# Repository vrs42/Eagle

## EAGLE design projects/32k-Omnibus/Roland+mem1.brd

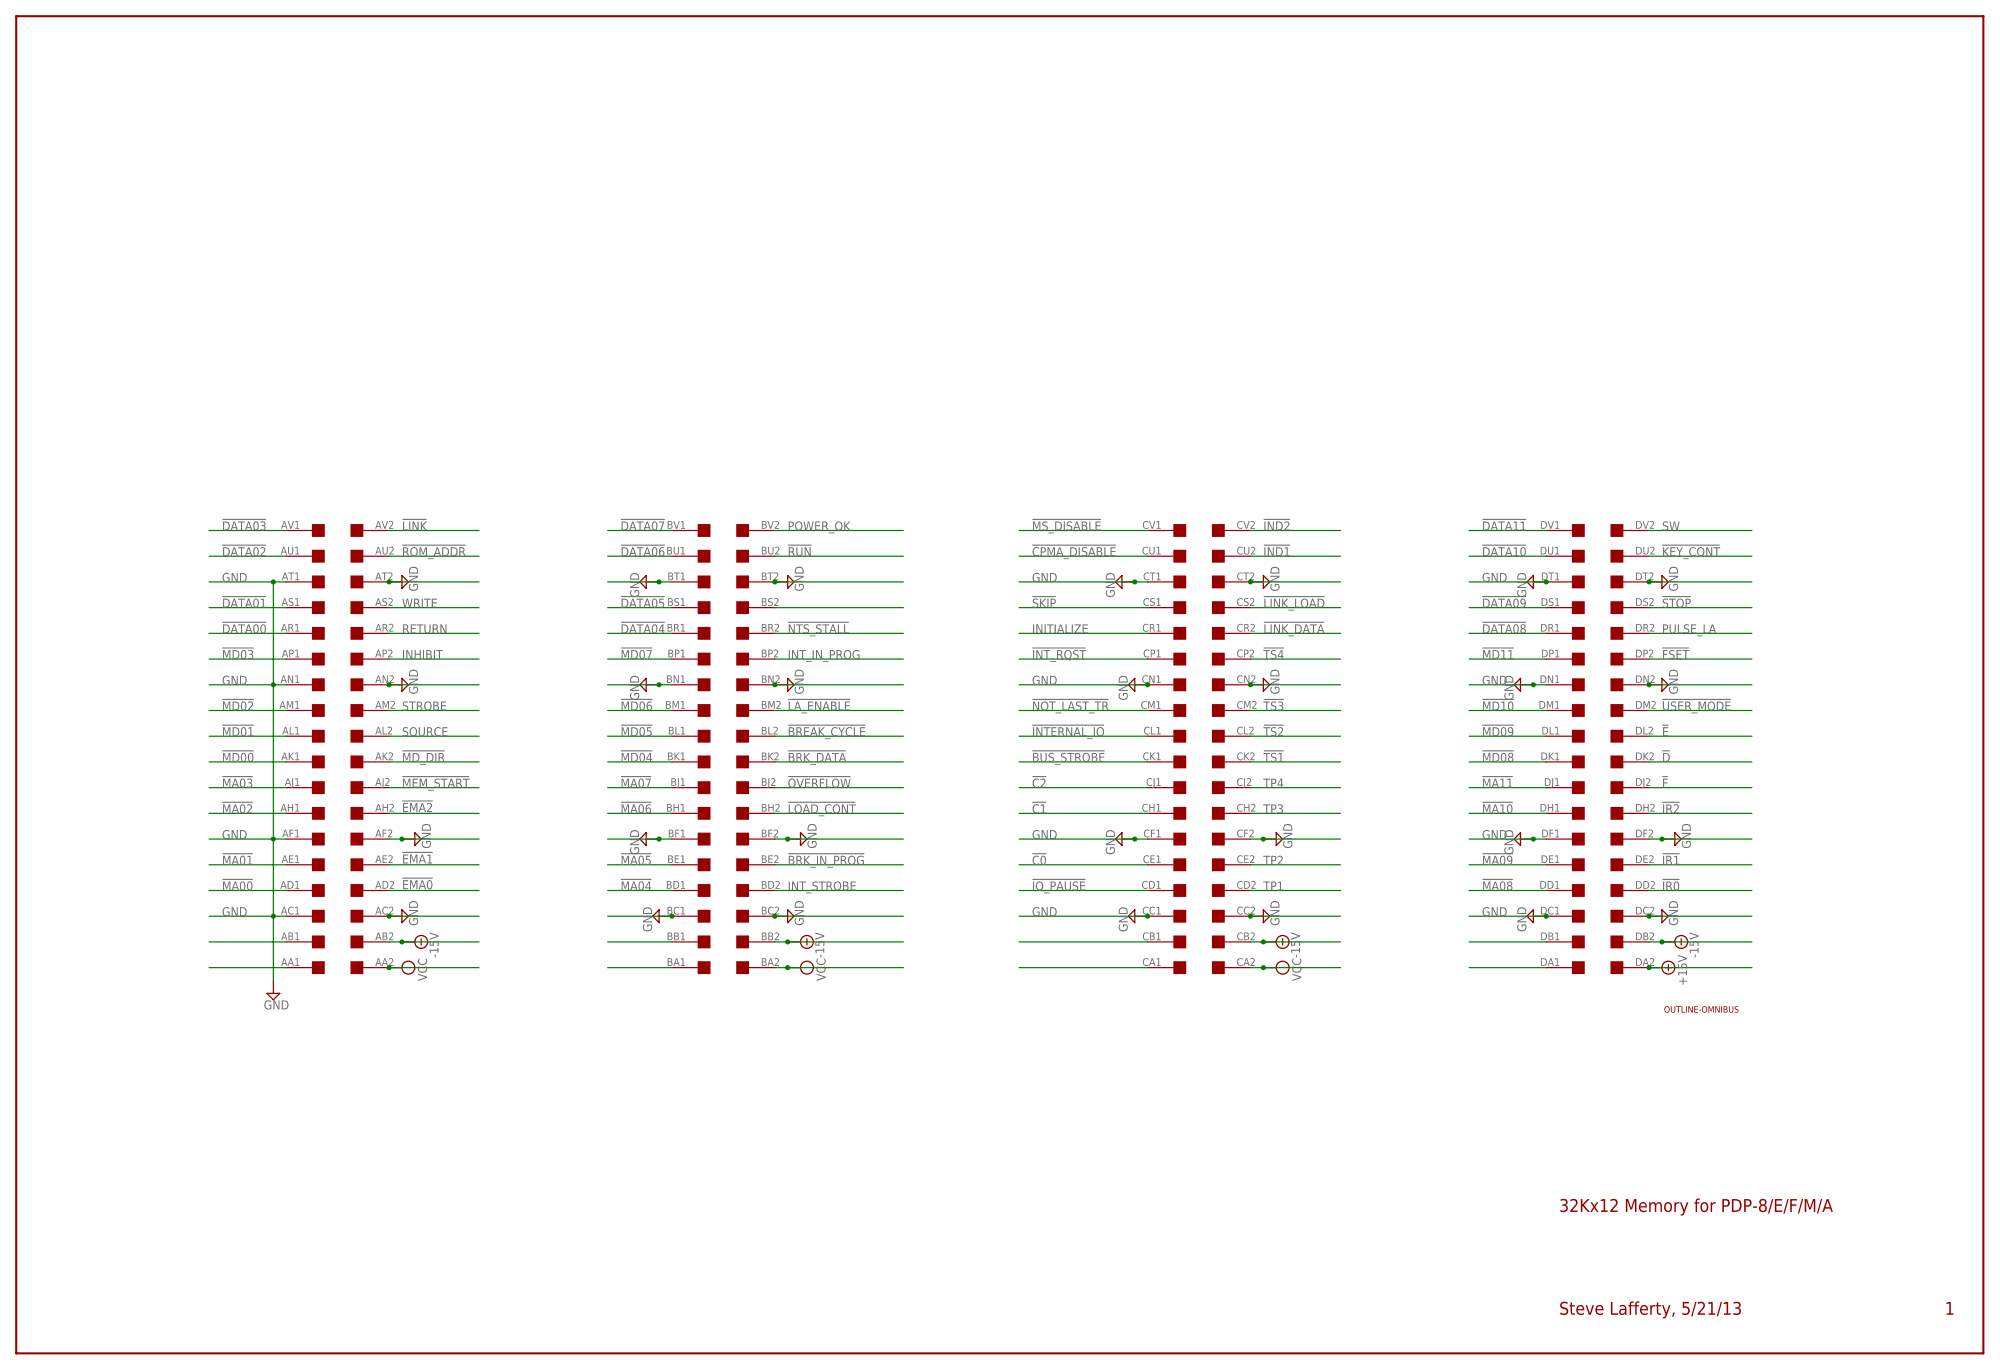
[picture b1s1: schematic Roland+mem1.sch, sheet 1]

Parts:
J1: EDGE; EDGE-CON8
U$1: OUTLINE-OMNIBUS; OMNIBUS

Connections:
!BREAK_CYCLE: J1.BL2
!BRK_DATA: J1.BK2; also elsewhere on the board
!BRK_IN_PROG: J1.BE2
!BUS_STROBE: J1.CK1
!C0: J1.CE1
!C1: J1.CH1
!C2: J1.CJ1
!CPMA_DISABLE: J1.CU1
!D: J1.DK2
!DATA00: J1.AR1; also elsewhere on the board
!DATA01: J1.AS1; also elsewhere on the board
!DATA02: J1.AU1; also elsewhere on the board
!DATA03: J1.AV1; also elsewhere on the board
!DATA04: J1.BR1; also elsewhere on the board
!DATA05: J1.BS1; also elsewhere on the board
!DATA06: J1.BU1; also elsewhere on the board
!DATA07: J1.BV1; also elsewhere on the board
!DATA08: J1.DR1; also elsewhere on the board
!DATA09: J1.DS1; also elsewhere on the board
!DATA10: J1.DU1; also elsewhere on the board
!DATA11: J1.DV1; also elsewhere on the board
!E: J1.DL2
!EMA0: J1.AD2; also elsewhere on the board
!EMA1: J1.AE2; also elsewhere on the board
!EMA2: J1.AH2; also elsewhere on the board
!F: J1.DJ2
!FSET: J1.DP2
!IND1: J1.CU2
!IND2: J1.CV2
!INTERNAL_IO: J1.CL1
!INT_RQST: J1.CP1
!IO_PAUSE: J1.CD1
!IR0: J1.DD2
!IR1: J1.DE2
!IR2: J1.DH2
!KEY_CONT: J1.DU2; also elsewhere on the board
!LA_ENABLE: J1.BM2; also elsewhere on the board
!LINK: J1.AV2
!LINK_DATA: J1.CR2
!LINK_LOAD: J1.CS2
!LOAD_CONT: J1.BH2
!MA00: J1.AD1; also elsewhere on the board
!MA01: J1.AE1; also elsewhere on the board
!MA02: J1.AH1; also elsewhere on the board
!MA03: J1.AJ1; also elsewhere on the board
!MA04: J1.BD1; also elsewhere on the board
!MA05: J1.BE1; also elsewhere on the board
!MA06: J1.BH1; also elsewhere on the board
!MA07: J1.BJ1; also elsewhere on the board
!MA08: J1.DD1; also elsewhere on the board
!MA09: J1.DE1; also elsewhere on the board
!MA10: J1.DH1; also elsewhere on the board
!MA11: J1.DJ1; also elsewhere on the board
!MD00: J1.AK1; also elsewhere on the board
!MD01: J1.AL1; also elsewhere on the board
!MD02: J1.AM1; also elsewhere on the board
!MD03: J1.AP1; also elsewhere on the board
!MD04: J1.BK1; also elsewhere on the board
!MD05: J1.BL1; also elsewhere on the board
!MD06: J1.BM1; also elsewhere on the board
!MD07: J1.BP1; also elsewhere on the board
!MD08: J1.DK1; also elsewhere on the board
!MD09: J1.DL1; also elsewhere on the board
!MD10: J1.DM1; also elsewhere on the board
!MD11: J1.DP1; also elsewhere on the board
!MD_DIR: J1.AK2; also elsewhere on the board
!MEM_START: J1.AJ2; also elsewhere on the board
!MS_DISABLE: J1.CV1; also elsewhere on the board
!NOT_LAST_TR: J1.CM1
!NTS_STALL: J1.BR2
!OVERFLOW: J1.BJ2
!ROM_ADDR: J1.AU2; also elsewhere on the board
!RUN: J1.BU2; also elsewhere on the board
!SKIP: J1.CS1
!STOP: J1.DS2; also elsewhere on the board
!TS1: J1.CK2
!TS2: J1.CL2
!TS3: J1.CM2
!TS4: J1.CP2; also elsewhere on the board
!USER_MODE: J1.DM2
+15V: J1.DA2
-15V: J1.AB2, J1.BB2, J1.CB2, J1.DB2
GND: J1.AC1, J1.AC2, J1.AF1, J1.AF2, J1.AN1, J1.AN2, J1.AT1, J1.AT2, J1.BC1, J1.BC2, J1.BF1, J1.BF2, J1.BN1, J1.BN2, J1.BT1, J1.BT2, J1.CC1, J1.CC2, J1.CF1, J1.CF2, J1.CN1, J1.CN2, J1.CT1, J1.CT2, J1.DC1, J1.DC2, J1.DF1, J1.DF2, J1.DN1, J1.DN2, J1.DT1, J1.DT2; also elsewhere on the board
INHIBIT: J1.AP2
INITIALIZE: J1.CR1; also elsewhere on the board
INT_IN_PROG: J1.BP2
INT_STROBE: J1.BD2
POWER_OK: J1.BV2; also elsewhere on the board
PULSE_LA: J1.DR2; also elsewhere on the board
RETURN: J1.AR2
SOURCE: J1.AL2; also elsewhere on the board
STROBE: J1.AM2
SW: J1.DV2; also elsewhere on the board
TP1: J1.CD2
TP2: J1.CE2
TP3: J1.CH2
TP4: J1.CJ2; also elsewhere on the board
VCC: J1.AA2, J1.BA2, J1.CA2; also elsewhere on the board
WRITE: J1.AS2; also elsewhere on the board

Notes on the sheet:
32Kx12 Memory for PDP-8/E/F/M/A
Steve Lafferty, 5/21/13

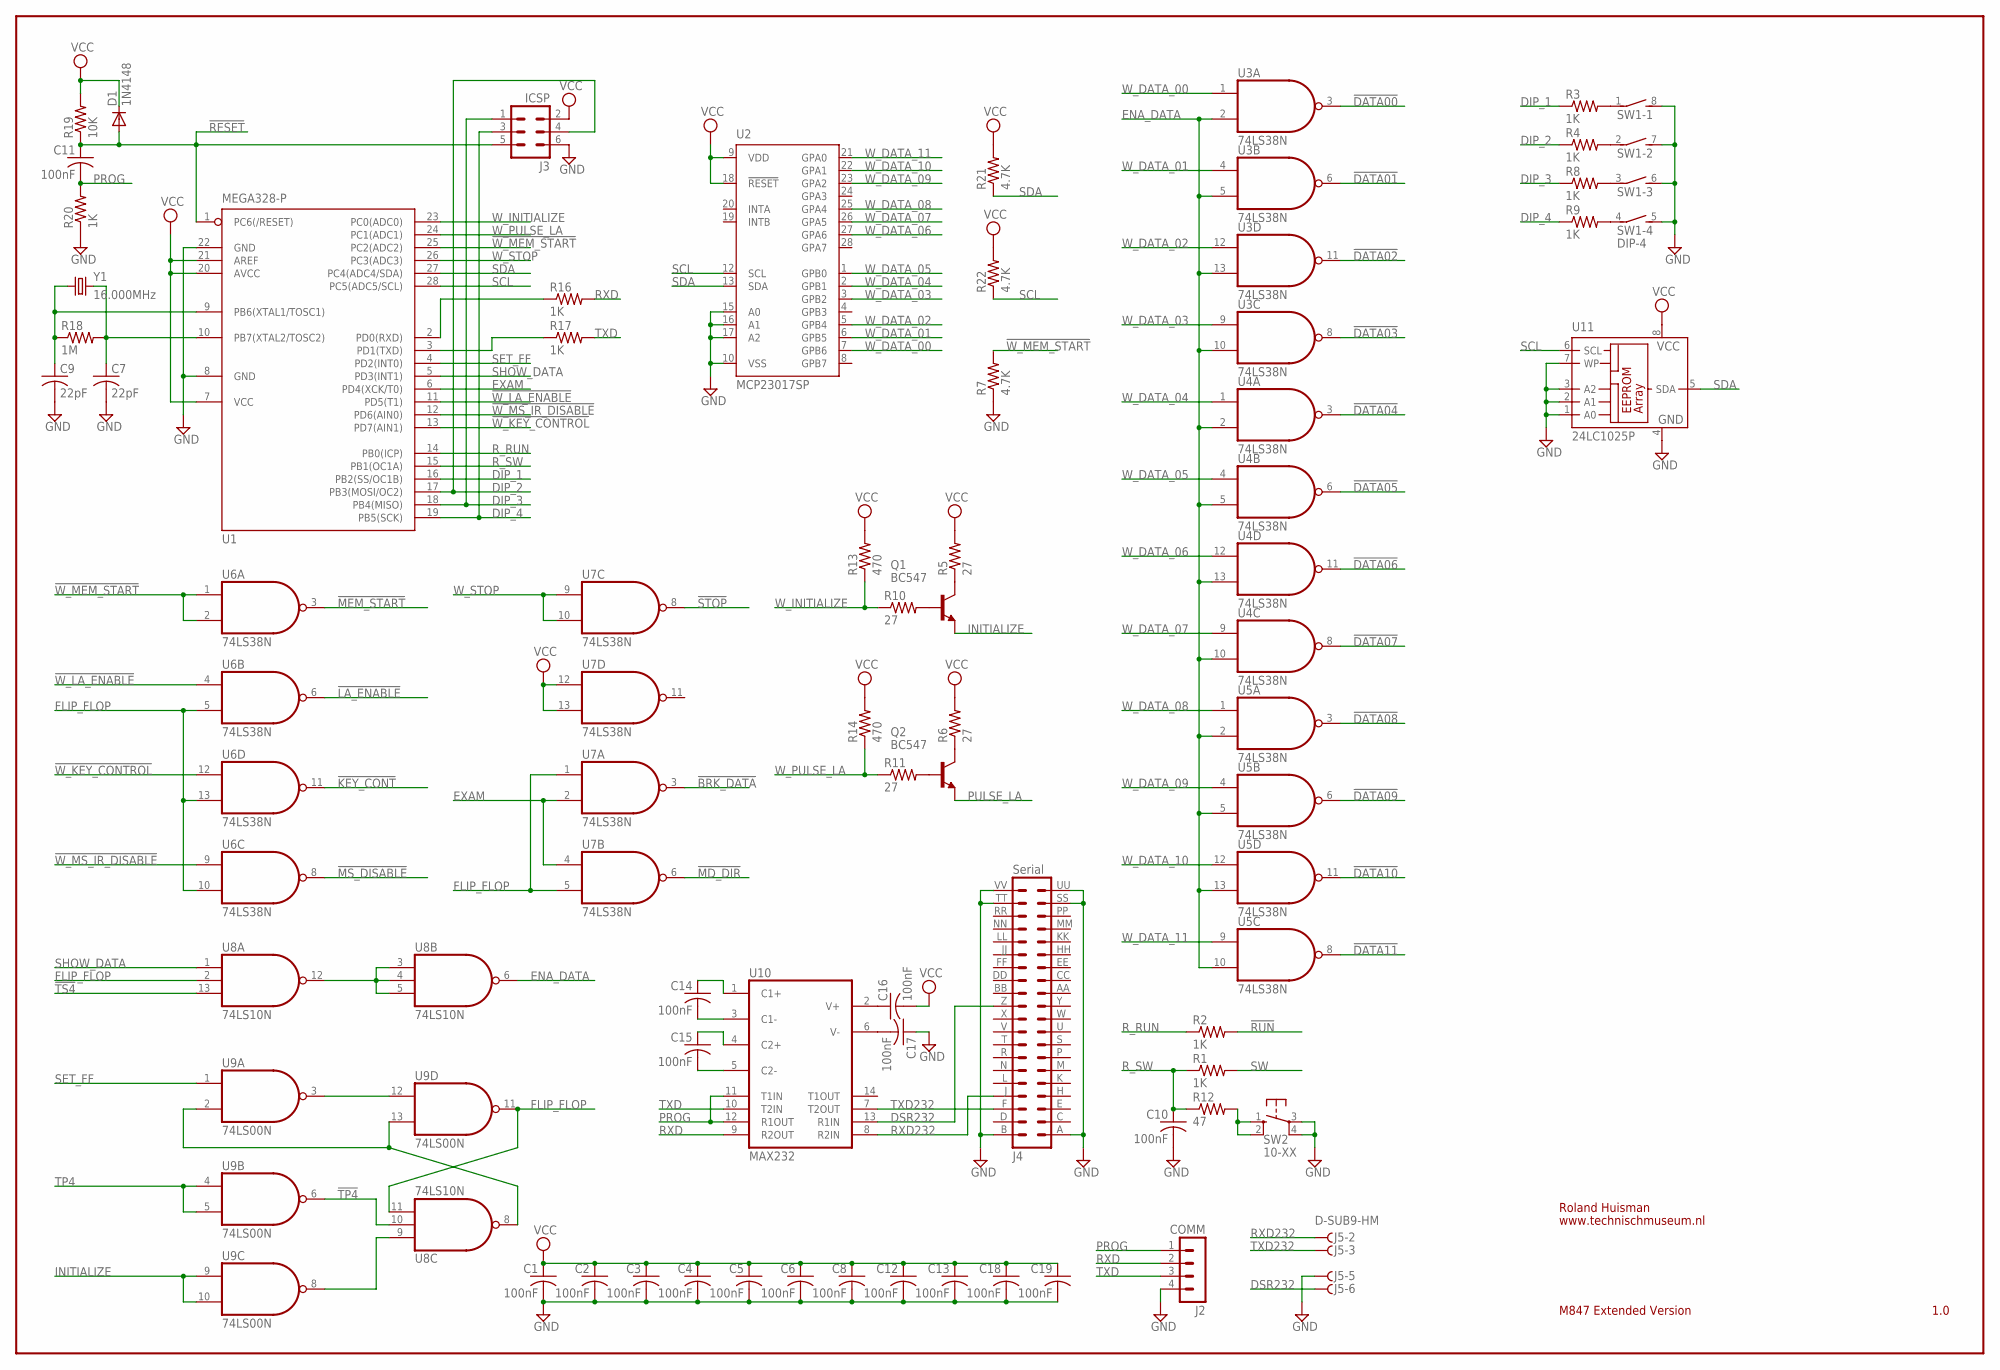
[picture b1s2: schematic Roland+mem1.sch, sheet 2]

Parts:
C1, C2, C3, C4, C5, C6, C8, C10, C11, C12, C13, C14, C15, C16, C17, C18, C19: 100nF; C050-025X075
C7, C9: 22pF; C050-025X075
D1: 1N4148; DO35-10
J2: COMM; MA04-1
J3: ICSP; MA03-2
J4: Serial; DEC40PINH
J5: D-SUB9-HM; H5M09RA
Q1, Q2: BC547; TO5
R1, R2, R3, R4, R8, R9, R16, R17, R20: 1K; 0207/10
R5, R6, R10, R11: 27; 0207/10
R7, R21, R22: 4.7K; 0207/10
R12: 47; 0207/10
R13, R14: 470; 0207/10
R18: 1M; 0207/10
R19: 10K; 0207/10
SW1: DIP-4; DIP04S
SW2: 10-XX; B3F-10XX
U1: MEGA328-P; DIL28-3
U2: MCP23017SP; DIL28-3
U3, U4, U5, U6, U7: 74LS38N; DIL14
U8: 74LS10N; DIL14
U9: 74LS00N; DIL14
U10: MAX232; DIL16
U11: 24LC1025P; DIL8
Y1: 16.000MHz; HC49U-H

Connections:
!BRK_DATA: U7.3 (O); also elsewhere on the board
!DATA00: U3.3 (O); also elsewhere on the board
!DATA01: U3.6 (O); also elsewhere on the board
!DATA02: U3.11 (O); also elsewhere on the board
!DATA03: U3.8 (O); also elsewhere on the board
!DATA04: U4.3 (O); also elsewhere on the board
!DATA05: U4.6 (O); also elsewhere on the board
!DATA06: U4.11 (O); also elsewhere on the board
!DATA07: U4.8 (O); also elsewhere on the board
!DATA08: U5.3 (O); also elsewhere on the board
!DATA09: U5.6 (O); also elsewhere on the board
!DATA10: U5.11 (O); also elsewhere on the board
!DATA11: U5.8 (O); also elsewhere on the board
!KEY_CONT: U6.11 (O); also elsewhere on the board
!LA_ENABLE: U6.6 (O); also elsewhere on the board
!MD_DIR: U7.6 (O); also elsewhere on the board
!MEM_START: U6.3 (O); also elsewhere on the board
!MS_DISABLE: U6.8 (O); also elsewhere on the board
!RESET: C11.1, D1.A, J3.5, R19.1, U1.1 (PC6(/RESET))
!RUN: R2.2; also elsewhere on the board
!STOP: U7.8 (O); also elsewhere on the board
!TP4: U8.10 (I1), U9.6 (O)
!TS4: U8.13 (I2); also elsewhere on the board
!W_KEY_CONTROL: U1.13 (PD7(AIN1)), U6.12 (I0)
!W_LA_ENABLE: U1.11 (PD5(T1)), U6.4 (I0)
!W_MEM_START: R7.2, U1.25 (PC2(ADC2)), U6.1 (I0), U6.2 (I1)
!W_MS_IR_DISABLE: U1.12 (PD6(AIN0)), U6.9 (I0)
DIP_1: R3.1, U1.16 (PB2(SS/OC1B))
DIP_2: J3.4, R4.1, U1.17 (PB3(MOSI/OC2))
DIP_3: J3.1, R8.1, U1.18 (PB4(MISO))
DIP_4: J3.3, R9.1, U1.19 (PB5(SCK))
DSR232: J4.Z (22), J5.6, U10.13 (R1IN)
ENA_DATA: U3.2 (I1), U3.5 (I1), U3.10 (I1), U3.13 (I1), U4.2 (I1), U4.5 (I1), U4.10 (I1), U4.13 (I1), U5.2 (I1), U5.5 (I1), U5.10 (I1), U5.13 (I1), U8.6 (O)
EXAM: U1.6 (PD4(XCK/T0)), U7.2 (I1), U7.4 (I0)
FLIP_FLOP: U6.5 (I1), U6.10 (I1), U6.13 (I1), U7.1 (I0), U7.5 (I1), U8.2 (I1), U8.11 (I2), U9.11 (O)
GND: C1.2, C2.2, C3.2, C4.2, C5.2, C6.2, C7.2, C8.2, C9.2, C10.2, C12.2, C13.2, C17.1, C18.2, C19.2, J2.4, J3.6, J4.A (1), J4.B (2), J4.SS (37), J4.TT (38), J4.UU (39), J4.VV (40), J5.5, R7.1, R20.1, SW1.5 (2), SW1.6 (2), SW1.7 (2), SW1.8 (2), SW2.3, SW2.4 (P1), U1.8 (GND), U1.22 (GND), U2.10 (VSS), U2.15 (A0), U2.16 (A1), U2.17 (A2), U3.7 (GND), U4.7 (GND), U5.7 (GND), U6.7 (GND), U7.7 (GND), U8.7 (GND), U9.7 (GND), U10.15 (GND), U11.1 (A0), U11.2 (A1), U11.3 (A2), U11.4 (GND), U11.7 (WP); also elsewhere on the board
INITIALIZE: Q1.1 (E), U9.9 (I0), U9.10 (I1); also elsewhere on the board
unnamed: C7.1, R18.2, U1.10 (PB7(XTAL2/TOSC2)), Y1.1
unnamed: C9.1, R18.1, U1.9 (PB6(XTAL1/TOSC1)), Y1.2
unnamed: Q1.3 (C), R5.1
unnamed: Q1.2 (B), R10.2
unnamed: Q2.3 (C), R6.1
unnamed: Q2.2 (B), R11.2
unnamed: U9.3 (O), U9.12 (I0)
unnamed: U8.3 (I0), U8.4 (I1), U8.5 (I2), U8.12 (O)
unnamed: U8.8 (O), U9.2 (I1), U9.13 (I1)
unnamed: R17.1, U1.3 (PD1(TXD))
unnamed: R16.1, U1.2 (PD0(RXD))
unnamed: U8.9 (I0), U9.8 (O)
unnamed: C17.2, U10.6 (V-)
unnamed: C14.1, U10.1 (C1+)
unnamed: C14.2, U10.3 (C1-)
unnamed: C15.2, U10.5 (C2-)
unnamed: C15.1, U10.4 (C2+)
unnamed: C16.1, U10.2 (V+)
unnamed: R12.2, SW2.1 (S), SW2.2 (S1)
unnamed: R3.2, SW1.1
unnamed: R4.2, SW1.2 (1)
unnamed: R8.2, SW1.3 (1)
unnamed: R9.2, SW1.4 (1)
PROG: C11.2, J2.1, R20.2, U10.11 (T1IN), U10.12 (R1OUT)
PULSE_LA: Q2.1 (E); also elsewhere on the board
RXD: J2.2, R16.2, U10.9 (R2OUT)
RXD232: J4.J (8), J5.2, U10.8 (R2IN)
R_RUN: R2.1, U1.14 (PB0(ICP))
R_SW: C10.1, R1.1, R12.1, U1.15 (PB1(OC1A))
SCL: R22.1, U1.28 (PC5(ADC5/SCL)), U2.12 (SCL), U11.6 (SCL)
SDA: R21.1, U1.27 (PC4(ADC4/SDA)), U2.13 (SDA), U11.5 (SDA)
SET_FF: U1.4 (PD2(INT0)), U9.1 (I0)
SHOW_DATA: U1.5 (PD3(INT1)), U8.1 (I0)
SW: R1.2; also elsewhere on the board
TP4: U9.4 (I0), U9.5 (I1); also elsewhere on the board
TXD: J2.3, R17.2, U10.10 (T2IN)
TXD232: J4.F (6), J5.3, U10.7 (T2OUT)
VCC: C1.1, C2.1, C3.1, C4.1, C5.1, C6.1, C8.1, C12.1, C13.1, C16.2, C18.1, C19.1, D1.C, J3.2, R5.2, R6.2, R13.2, R14.2, R19.2, R21.2, R22.2, U1.7 (VCC), U1.20 (AVCC), U1.21 (AREF), U2.9 (VDD), U2.18 (!RESET), U3.14 (VCC), U4.14 (VCC), U5.14 (VCC), U6.14 (VCC), U7.12 (I0), U7.13 (I1), U7.14 (VCC), U8.14 (VCC), U9.14 (VCC), U10.16 (VCC), U11.8 (VCC); also elsewhere on the board
W_DATA_00: U2.7 (GPB6), U3.1 (I0)
W_DATA_01: U2.6 (GPB5), U3.4 (I0)
W_DATA_02: U2.5 (GPB4), U3.12 (I0)
W_DATA_03: U2.3 (GPB2), U3.9 (I0)
W_DATA_04: U2.2 (GPB1), U4.1 (I0)
W_DATA_05: U2.1 (GPB0), U4.4 (I0)
W_DATA_06: U2.27 (GPA6), U4.12 (I0)
W_DATA_07: U2.26 (GPA5), U4.9 (I0)
W_DATA_08: U2.25 (GPA4), U5.1 (I0)
W_DATA_09: U2.23 (GPA2), U5.4 (I0)
W_DATA_10: U2.22 (GPA1), U5.12 (I0)
W_DATA_11: U2.21 (GPA0), U5.9 (I0)
W_INITIALIZE: R10.1, R13.1, U1.23 (PC0(ADC0))
W_PULSE_LA: R11.1, R14.1, U1.24 (PC1(ADC1))
W_STOP: U1.26 (PC3(ADC3)), U7.9 (I0), U7.10 (I1)

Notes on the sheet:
D-SUB9-HM
M847 Extended Version
Roland Huisman
1.0
www.technischmuseum.nl

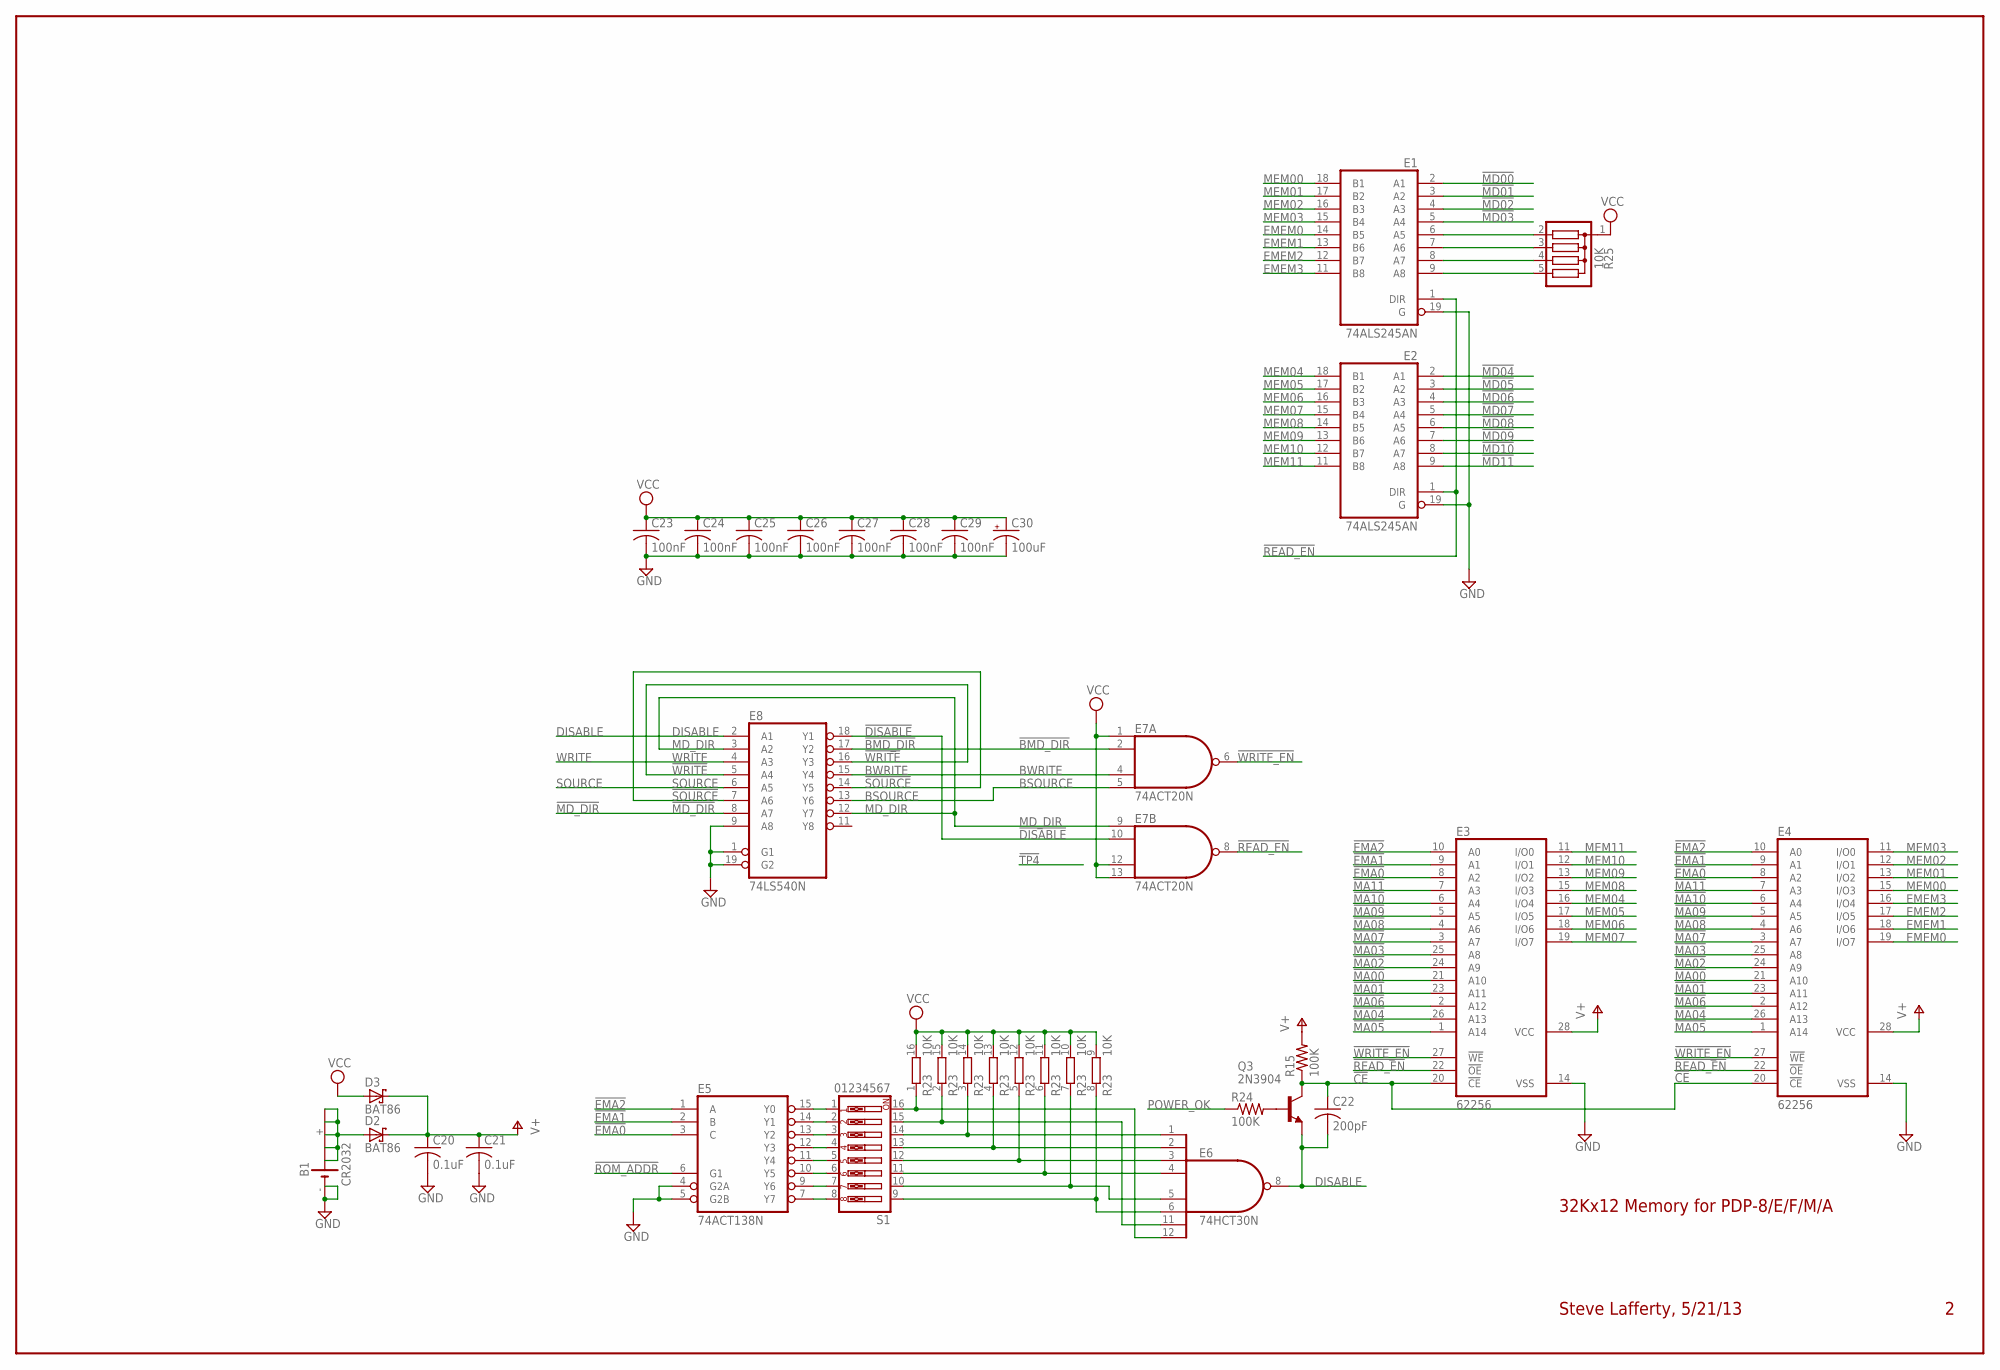
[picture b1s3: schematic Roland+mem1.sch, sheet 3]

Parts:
B1: CR2032; B2430UNI
C20, C21: 0.1uF; C050-025X075
C22: 200pF; C050-025X075
C23, C24, C25, C26, C27, C28, C29: 100nF; C050-025X075
C30: 100uF; E12-8
D2, D3: BAT86; DO35-10
E1, E2: 74ALS245AN; DIL20
E3, E4: 62256; DIL28-6
E5: 74ACT138N; DIL16
E6: 74HCT30N; DIL14
E7: 74ACT20N; DIL14
E8: 74LS540N; DIL20
Q3: 2N3904; TO92
R15, R24: 100K; 0207/10
R23: 10K; DIL16
R25: 10K; SIL5
S1: 01234567; EDG-08

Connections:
!BMD_DIR: E7.2 (I1), E8.17 (Y2)
!CE: C22.1, E3.20 (!CE), E4.20 (!CE), Q3.1 (C), R15.1
!DISABLE: E7.10 (I1), E8.18 (Y1)
!EMA0: E3.8 (A2), E4.8 (A2), E5.3 (C); also elsewhere on the board
!EMA1: E3.9 (A1), E4.9 (A1), E5.2 (B); also elsewhere on the board
!EMA2: E3.10 (A0), E4.10 (A0), E5.1 (A); also elsewhere on the board
!MA00: E3.21 (A10), E4.21 (A10); also elsewhere on the board
!MA01: E3.23 (A11), E4.23 (A11); also elsewhere on the board
!MA02: E3.24 (A9), E4.24 (A9); also elsewhere on the board
!MA03: E3.25 (A8), E4.25 (A8); also elsewhere on the board
!MA04: E3.26 (A13), E4.26 (A13); also elsewhere on the board
!MA05: E3.1 (A14), E4.1 (A14); also elsewhere on the board
!MA06: E3.2 (A12), E4.2 (A12); also elsewhere on the board
!MA07: E3.3 (A7), E4.3 (A7); also elsewhere on the board
!MA08: E3.4 (A6), E4.4 (A6); also elsewhere on the board
!MA09: E3.5 (A5), E4.5 (A5); also elsewhere on the board
!MA10: E3.6 (A4), E4.6 (A4); also elsewhere on the board
!MA11: E3.7 (A3), E4.7 (A3); also elsewhere on the board
!MD00: E1.2 (A1); also elsewhere on the board
!MD01: E1.3 (A2); also elsewhere on the board
!MD02: E1.4 (A3); also elsewhere on the board
!MD03: E1.5 (A4); also elsewhere on the board
!MD04: E2.2 (A1); also elsewhere on the board
!MD05: E2.3 (A2); also elsewhere on the board
!MD06: E2.4 (A3); also elsewhere on the board
!MD07: E2.5 (A4); also elsewhere on the board
!MD08: E2.6 (A5); also elsewhere on the board
!MD09: E2.7 (A6); also elsewhere on the board
!MD10: E2.8 (A7); also elsewhere on the board
!MD11: E2.9 (A8); also elsewhere on the board
!MD_DIR: E8.8 (A7); also elsewhere on the board
!READ_EN: E1.1 (DIR), E2.1 (DIR), E3.22 (!OE), E4.22 (!OE), E7.8 (O)
!ROM_ADDR: E5.6 (G1); also elsewhere on the board
!SOURCE: E8.7 (A6), E8.14 (Y5)
!WRITE: E8.5 (A4), E8.16 (Y3)
!WRITE_EN: E3.27 (!WE), E4.27 (!WE), E7.6 (O)
BSOURCE: E7.5 (I3), E8.13 (Y6)
BWRITE: E7.4 (I2), E8.15 (Y4)
DISABLE: C22.2, E6.8 (O), E8.2 (A1), Q3.3 (E)
EMEM0: E1.14 (B5), E4.19 (I/O7)
EMEM1: E1.13 (B6), E4.18 (I/O6)
EMEM2: E1.12 (B7), E4.17 (I/O5)
EMEM3: E1.11 (B8), E4.16 (I/O4)
GND: B1.-, B1.-@1 (-), C20.2, C21.2, C23.2, C24.2, C25.2, C26.2, C27.2, C28.2, C29.2, C30.-, E1.10 (GND), E1.19 (G), E2.10 (GND), E2.19 (G), E3.14 (VSS), E4.14 (VSS), E5.4 (G2A), E5.5 (G2B), E5.8 (GND), E6.7 (GND), E7.7 (GND), E8.1 (G1), E8.9 (A8), E8.10 (GND), E8.19 (G2); also elsewhere on the board
MD_DIR: E7.9 (I0), E8.3 (A2), E8.12 (Y7)
MEM00: E1.18 (B1), E4.15 (I/O3)
MEM01: E1.17 (B2), E4.13 (I/O2)
MEM02: E1.16 (B3), E4.12 (I/O1)
MEM03: E1.15 (B4), E4.11 (I/O0)
MEM04: E2.18 (B1), E3.16 (I/O4)
MEM05: E2.17 (B2), E3.17 (I/O5)
MEM06: E2.16 (B3), E3.18 (I/O6)
MEM07: E2.15 (B4), E3.19 (I/O7)
MEM08: E2.14 (B5), E3.15 (I/O3)
MEM09: E2.13 (B6), E3.13 (I/O2)
MEM10: E2.12 (B7), E3.12 (I/O1)
MEM11: E2.11 (B8), E3.11 (I/O0)
unnamed: E5.7 (Y7), S1.8
unnamed: E5.9 (Y6), S1.7
unnamed: E5.10 (Y5), S1.6
unnamed: E5.11 (Y4), S1.5
unnamed: E5.12 (Y3), S1.4
unnamed: E5.13 (Y2), S1.3
unnamed: E5.14 (Y1), S1.2
unnamed: E5.15 (Y0), S1.1
unnamed: B1.+, B1.+@1 (+), B1.+@2 (+), B1.+@3 (+), B1.+@4 (+), D2.A
unnamed: E6.2 (I1), R23.4 (1), S1.13
unnamed: E6.1 (I0), R23.3 (1), S1.14
unnamed: E6.3 (I2), R23.5 (1), S1.12
unnamed: E6.4 (I3), R23.6 (1), S1.11
unnamed: E6.5 (I4), R23.7 (1), S1.10
unnamed: E6.6 (I5), R23.8 (1), S1.9
unnamed: E6.12 (I7), R23.1, S1.16
unnamed: E6.11 (I6), R23.2 (1), S1.15
unnamed: Q3.2 (B), R24.2
unnamed: E1.6 (A5), R25.2
unnamed: E1.9 (A8), R25.5
unnamed: E1.8 (A7), R25.4
unnamed: E1.7 (A6), R25.3
POWER_OK: R24.1; also elsewhere on the board
SOURCE: E8.6 (A5); also elsewhere on the board
V+: C20.1, C21.1, D2.C, D3.C, E3.28 (VCC), E4.28 (VCC), R15.2
VCC: C23.1, C24.1, C25.1, C26.1, C27.1, C28.1, C29.1, C30.+, D3.A, E1.20 (VCC), E2.20 (VCC), E5.16 (VCC), E6.14 (VCC), E7.1 (I0), E7.12 (I2), E7.13 (I3), E7.14 (VCC), E8.20 (VCC), R23.9 (2), R23.10 (2), R23.11 (2), R23.12 (2), R23.13 (2), R23.14 (2), R23.15 (2), R23.16 (2), R25.1; also elsewhere on the board
WRITE: E8.4 (A3); also elsewhere on the board

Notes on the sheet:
32Kx12 Memory for PDP-8/E/F/M/A
Steve Lafferty, 5/21/13

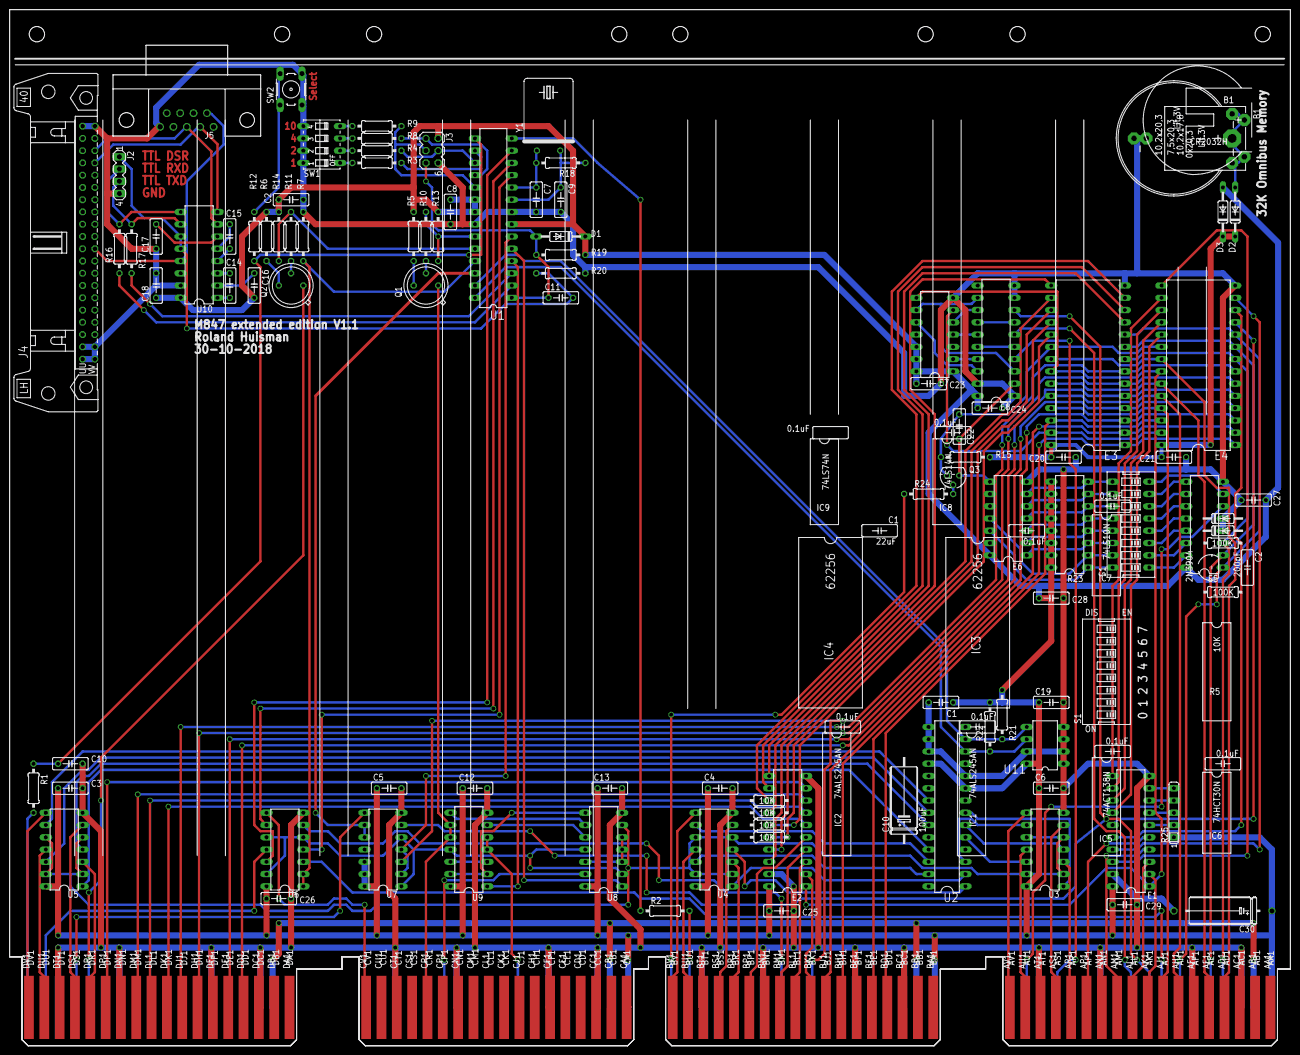
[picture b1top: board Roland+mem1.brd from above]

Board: 2 copper layers, 265.3 x 214.6 mm, 91 parts (0 on the bottom side), 172 nets.

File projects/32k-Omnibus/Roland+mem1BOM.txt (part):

Partlist exported from C:/Users/Vince/Documents/Eagle/projects/32k-Omnibus/Roland+mem.sch at 1/29/2019 4:17:25 PM

Qty Value           Device            Package      Parts                                                                                                           Description                                                MF        MPN           OC_FARNELL OC_NEWARK
2   0.1uF           C-US050-025X075   C050-025X075 C20, C21                                                                                                        CAPACITOR, American symbol                                                                             
1   01234567        SW_DIP-8          EDG-08       S1                                                                                                              DIP SWITCH                                                                                             
1   10-XX           10-XX             B3F-10XX     SW2                                                                                                             OMRON SWITCH                                                         B3F-1000      176432     36M3542  
2   100K            R-US_0207/10      0207/10      R15, R24                                                                                                        RESISTOR, American symbol                                                                              
24  100nF           C-US050-025X075   C050-025X075 C1, C2, C3, C4, C5, C6, C8, C10, C11, C12, C13, C14, C15, C16, C17, C18, C19, C23, C24, C25, C26, C27, C28, C29 CAPACITOR, American symbol                                                                             
1   100uF           CPOL-USE20-8AXIAL E12-8        C30                                                                                                             A 0.8 inch electrolytic.                                                                               
1   10K             8R-P              DIL16        R23                                                                                                             DIL RESISTOR                                                                                           
1   10K             G04R              SIL5         R25                                                                                                             SIL RESISTOR                                                                       unknown    unknown  
1   10K             R-US_0207/10      0207/10      R19                                                                                                             RESISTOR, American symbol                                                                              
1   16.000MHz       CRYSTALHC49U-H    HC49U-H      Y1                                                                                                              CRYSTAL                                                                            1666973    unknown  
9   1K              R-US_0207/10      0207/10      R1, R2, R3, R4, R8, R9, R16, R17, R20                                                                           RESISTOR, American symbol                                                                              
1   1M              R-US_0207/10      0207/10      R18                                                                                                             RESISTOR, American symbol                                                                              
1   1N4148          1N4148DO35-10     DO35-10      D1                                                                                                              DIODE                                                                                                  
1   200pF           C-US050-025X075   C050-025X075 C22                                                                                                             CAPACITOR, American symbol                                                                             
2   22pF            C-US050-025X075   C050-025X075 C7, C9                                                                                                          CAPACITOR, American symbol                                                                             
1   24LC1025P       24LC025P          DIL8         U11                                                                                                             Serial EEPROM                                              MICROCHIP 24LC025-I/P   unknown    92C7098  
4   27              R-US_0207/10      0207/10      R5, R6, R10, R11                                                                                                RESISTOR, American symbol                                                                              
1   2N3904          2N3904            TO92         Q3                                                                                                              NPN TRANSISTOR                                                                                         
3   4.7K            R-US_0207/10      0207/10      R7, R21, R22                                                                                                    RESISTOR, American symbol                                                                              
1   47              R-US_0207/10      0207/10      R12                                                                                                             RESISTOR, American symbol                                                                              
2   470             R-US_0207/10      0207/10      R13, R14                                                                                                        RESISTOR, American symbol                                                                              
2   62256           58C256P           DIL28-6      E3, E4                                                                                                          MEMORY                                                                                                 
1   74ACT138N       74LS138N          DIL16        E5                                                                                                              3-line to 8-line DECODER/DEMULTIPLEXER                                                                 
1   74ACT20N        74LS20N           DIL14        E7                                                                                                              Dual 4-input NAND gate                                                                                 
2   74ALS245AN      74LS245N          DIL20        E1, E2                                                                                                          Octal BUS TRANSCEIVER, 3-state                                                                         
1   74HCT30N        74LS30N           DIL14        E6                                                                                                              8-input NAND gate                                                                                      
1   74LS00N         74LS00N           DIL14        U9                                                                                                              Quad 2-input NAND gate                                                                                 
1   74LS10N         74LS10N           DIL14        U8                                                                                                              Triple 3-input NAND gate                                                                               
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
